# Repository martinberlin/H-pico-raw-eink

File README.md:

# H-pico-raw-eink

This is just a prototype PCB to test parallel eink signals with Raspberry PICO.

## Important To-Dos:

Find out if the pins selected for P-Mic signals and EINK signals behave correctly and are capable to do the job.

## Relevant datasheets

High voltages required by EPD P-Mic

https://www.ti.com/product/TPS65185

Eink signals described by Petteri Aimonen

http://essentialscrap.com/eink/waveforms.html

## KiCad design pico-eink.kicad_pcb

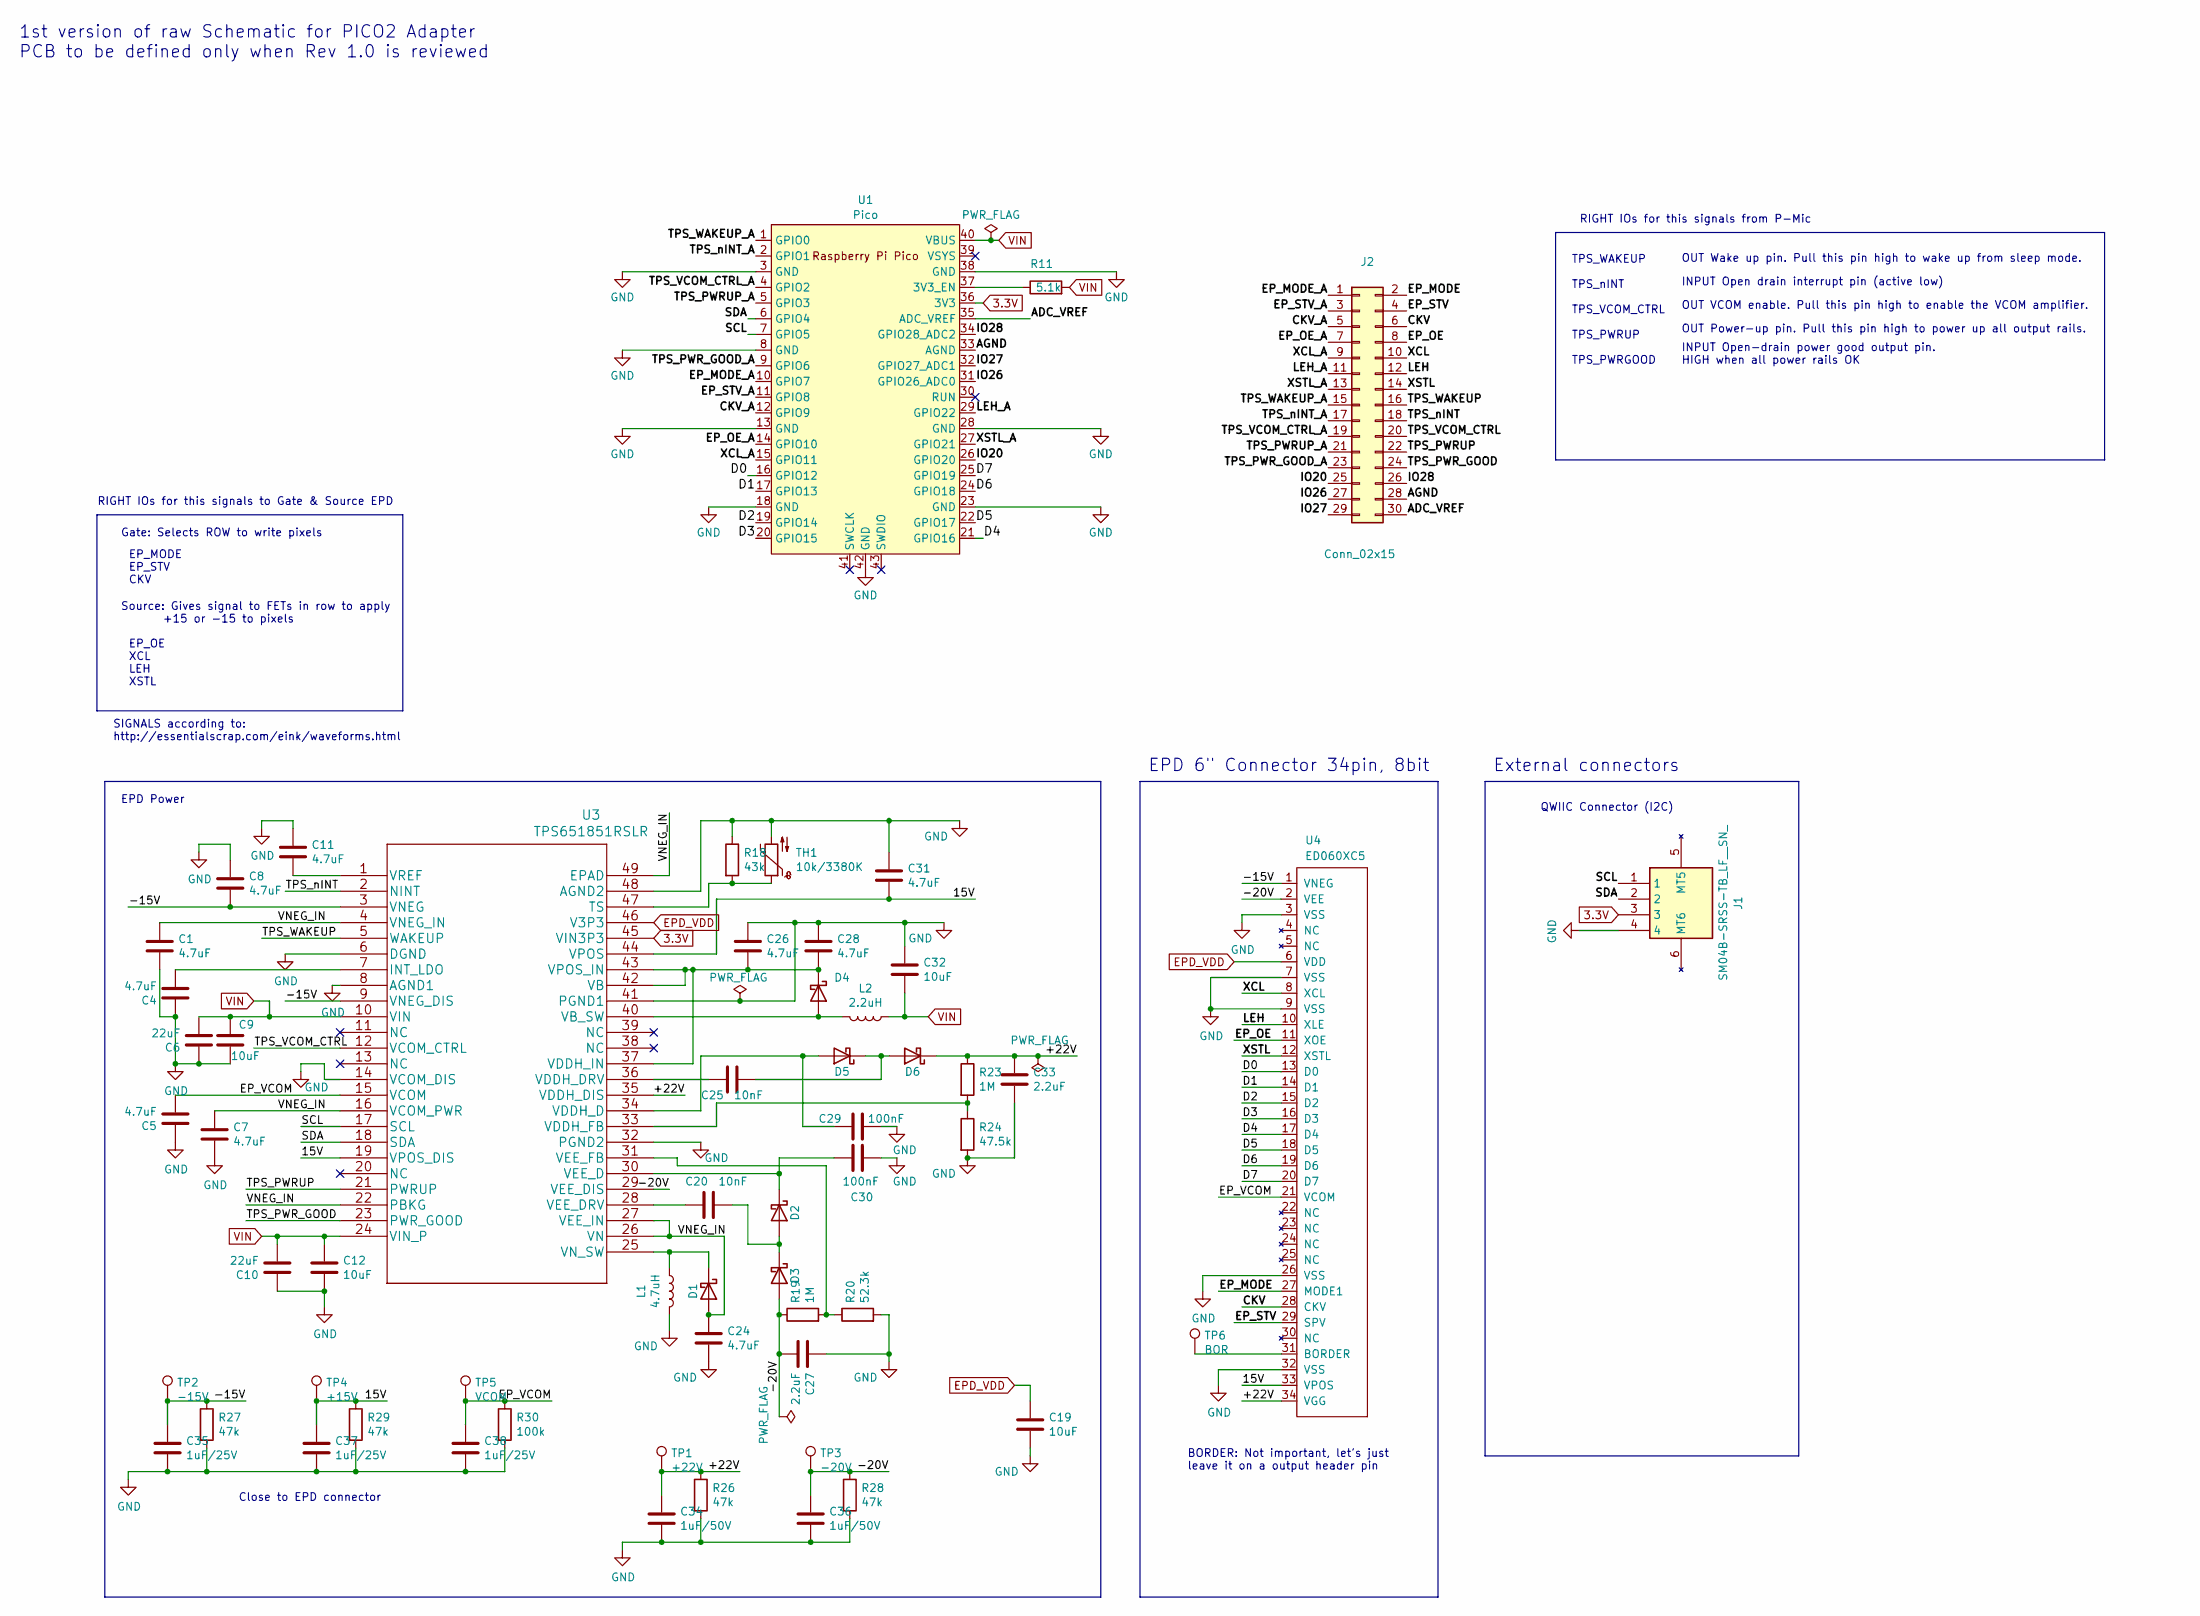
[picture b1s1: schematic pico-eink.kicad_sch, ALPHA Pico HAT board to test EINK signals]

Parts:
C1, C4, C5, C7, C8, C11, C24, C26, C28, C31: 4.7uF; C_0805_2012Metric; LCSC C1779
C6, C10: 22uF; C_0805_2012Metric; LCSC C45783
C9, C12, C19, C32: 10uF; C_0805_2012Metric; LCSC C15850
C20, C25: 10nF; C_0805_2012Metric; LCSC C1710
C27, C33: 2.2uF; C_0805_2012Metric; LCSC C49217
C29, C30: 100nF; C_0805_2012Metric; LCSC C49678
C34, C36: 1uF/50V; C_1206_3216Metric; LCSC C1848
C35, C37, C38: 1uF/25V; C_0805_2012Metric; LCSC C28323
D1, D2, D3, D4, D5, D6: MBR0540; D_SOD-123; LCSC C21353
J1: SM04B-SRSS-TB_LF__SN_; QWIIC_SM04B-SRSS-TB_LFSN_; Manufacturer_Part_Number SM04B-SRSS-TB(LF)(SN); LCSC C160404
J2: Conn_02x15; PinHeader_2x15_P2.54mm_Vertical
L1: 4.7uH; L_Taiyo-Yuden_NR-50xx_HandSoldering; LCSC C222947
L2: 2.2uH; L_Taiyo-Yuden_NR-40xx_HandSoldering; LCSC C92959
R11: 5.1k; R_0603_1608Metric; LCSC C23186
R18: 43k; R_0603_1608Metric; LCSC C23172
R19, R23: 1M; R_0603_1608Metric; LCSC C22935
R20: 52.3k; R_0603_1608Metric; LCSC C23196
R24: 47.5k; R_0603_1608Metric; LCSC C25819
R26, R27, R28, R29: 47k; R_0603_1608Metric; LCSC C25819
R30: 100k; R_0603_1608Metric; LCSC C25803
TH1: 10k/3380K; R_0603_1608Metric; LCSC C76589
TP1: +22V; TestPoint_Pad_D2.5mm
TP2: -15V; TestPoint_Pad_D2.5mm
TP3: -20V; TestPoint_Pad_D2.5mm
TP4: +15V; TestPoint_Pad_D2.5mm
TP5: VCOM; TestPoint_Pad_D2.5mm
TP6: BOR; TestPoint_Pad_D2.5mm
U1: Pico; RPi_Pico_SMD_TH
U3: TPS651851RSLR; LCSC C139292
U4: ED060XC5; X05A20H34G; LCSC C528053

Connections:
3.3V: J1.3, U1.36 (3V3), U3.45 (VIN3P3)
/15V: C31.2, C37.1, R29.1, TP4.1, U3.19 (VPOS_DIS), U3.44 (VPOS), U4.33 (VPOS)
/+22V: C33.1, C34.1, D6.1 (K), R23.1, R26.1, TP1.1, U3.35 (VDDH_DIS), U4.34 (VGG)
/-15V: C8.2, C35.1, R27.1, TP2.1, U3.3 (VNEG), U3.9 (VNEG_DIS), U4.1 (VNEG)
/-20V: C27.2, C36.1, D3.2 (A), R19.1, R28.1, TP3.1, U3.29 (VEE_DIS), U4.2 (VEE)
/ADC_VREF: J2.30, U1.35 (ADC_VREF)
/AGND: J2.28, U1.33 (AGND)
/CKV: J2.6, U4.28 (CKV)
/CKV_A: J2.5, U1.12 (GPIO9)
/D0: U1.16 (GPIO12), U4.13 (D0)
/D1: U1.17 (GPIO13), U4.14 (D1)
/D2: U1.19 (GPIO14), U4.15 (D2)
/D3: U1.20 (GPIO15), U4.16 (D3)
/D4: U1.21 (GPIO16), U4.17 (D4)
/D5: U1.22 (GPIO17), U4.18 (D5)
/D6: U1.24 (GPIO18), U4.19 (D6)
/D7: U1.25 (GPIO19), U4.20 (D7)
/EP_MODE: J2.2, U4.27 (MODE1)
/EP_MODE_A: J2.1, U1.10 (GPIO7)
/EP_OE: J2.8, U4.11 (XOE)
/EP_OE_A: J2.7, U1.14 (GPIO10)
/EP_STV: J2.4, U4.29 (SPV)
/EP_STV_A: J2.3, U1.11 (GPIO8)
/EP_VCOM: C5.2, C38.1, R30.1, TP5.1, U3.15 (VCOM), U4.21 (VCOM)
/IO20: J2.25, U1.26 (GPIO20)
/IO26: J2.27, U1.31 (GPIO26_ADC0)
/IO27: J2.29, U1.32 (GPIO27_ADC1)
/IO28: J2.26, U1.34 (GPIO28_ADC2)
/LEH: J2.12, U4.10 (XLE)
/LEH_A: J2.11, U1.29 (GPIO22)
/SCL: J1.1, U1.7 (GPIO5), U3.17 (SCL)
/SDA: J1.2, U1.6 (GPIO4), U3.18 (SDA)
/TPS_PWRUP: J2.22, U3.21 (PWRUP)
/TPS_PWRUP_A: J2.21, U1.5 (GPIO3)
/TPS_PWR_GOOD: J2.24, U3.23 (PWR_GOOD)
/TPS_PWR_GOOD_A: J2.23, U1.9 (GPIO6)
/TPS_VCOM_CTRL: J2.20, U3.12 (VCOM_CTRL)
/TPS_VCOM_CTRL_A: J2.19, U1.4 (GPIO2)
/TPS_WAKEUP: J2.16, U3.5 (WAKEUP)
/TPS_WAKEUP_A: J2.15, U1.1 (GPIO0)
/TPS_nINT: J2.18, U3.2 (NINT)
/TPS_nINT_A: J2.17, U1.2 (GPIO1)
/VNEG_IN: C1.1, C7.1, C24.1, D1.2 (A), U3.4 (VNEG_IN), U3.16 (VCOM_PWR), U3.22 (PBKG), U3.26 (VN), U3.27 (VEE_IN), U3.49 (EPAD)
/XCL: J2.10, U4.8 (XCL)
/XCL_A: J2.9, U1.15 (GPIO11)
/XSTL: J2.14, U4.12 (XSTL)
/XSTL_A: J2.13, U1.27 (GPIO21)
EPD_VDD: C19.1, U3.46 (V3P3), U4.6 (VDD)
GND: C1.2, C4.1, C5.1, C6.1, C7.2, C8.1, C9.2, C10.1, C11.1, C12.2, C19.2, C24.2, C26.1, C27.1, C28.1, C29.1, C30.2, C31.1, C32.1, C33.2, C34.2, C35.2, C36.2, C37.2, C38.2, J1.4, L1.2, R18.1, R20.2, R24.2, R26.2, R27.2, R28.2, R29.2, R30.2, TH1.2, U1.3 (GND), U1.8 (GND), U1.13 (GND), U1.18 (GND), U1.23 (GND), U1.28 (GND), U1.38 (GND), U1.42 (GND), U3.6 (DGND), U3.8 (AGND1), U3.14 (VCOM_DIS), U3.32 (PGND2), U3.41 (PGND1), U3.48 (AGND2), U4.3 (VSS), U4.7 (VSS), U4.9 (VSS), U4.26 (VSS), U4.32 (VSS)
unnamed: D1.1 (K), L1.1, U3.25 (VN_SW)
unnamed: C20.1, D2.2 (A), D3.1 (K)
unnamed: C30.1, D2.1 (K), U3.30 (VEE_D)
unnamed: D4.2 (A), L2.2, U3.40 (VB_SW)
unnamed: C26.2, C28.2, D4.1 (K), U3.37 (VDDH_IN), U3.42 (VB), U3.43 (VPOS_IN)
unnamed: C29.2, D5.2 (A), U3.34 (VDDH_D)
unnamed: C25.1, D5.1 (K), D6.2 (A)
unnamed: R11.1, U1.37 (3V3_EN)
unnamed: C4.2, U3.7 (INT_LDO)
unnamed: R18.2, TH1.1, U3.47 (TS)
unnamed: C25.2, U3.36 (VDDH_DRV)
unnamed: R23.2, R24.1, U3.33 (VDDH_FB)
unnamed: C20.2, U3.28 (VEE_DRV)
unnamed: R19.2, R20.1, U3.31 (VEE_FB)
unnamed: C11.2, U3.1 (VREF)
unnamed: TP6.1, U4.31 (BORDER)
VIN: C6.2, C9.1, C10.2, C12.1, C32.2, L2.1, R11.2, U1.40 (VBUS), U3.10 (VIN), U3.24 (VIN_P)

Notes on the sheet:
BORDER: Not important, let's just leave it on a output header pin
Gate: Selects ROW to write pixels
Close to EPD connector
TPS_WAKEUP TPS_nINT TPS_VCOM_CTRL TPS_PWRUP TPS_PWRGOOD
EPD 6" Connector 34pin, 8bit
INPUT Open drain interrupt pin (active low)
SIGNALS according to: http://essentialscrap.com/eink/waveforms.html
Source: Gives signal to FETs in row to apply +15 or -15 to pixels
RIGHT IOs for this signals to Gate & Source EPD
INPUT Open-drain power good output pin. HIGH when all power rails OK
OUT VCOM enable. Pull this pin high to enable the VCOM amplifier.
QWIIC Connector (I2C)
EPD Power
RIGHT IOs for this signals from P-Mic
OUT Wake up pin. Pull this pin high to wake up from sleep mode.
1st version of raw Schematic for PICO2 Adapter PCB to be defined only when Rev 1.0 is reviewed
EP_OE XCL LEH XSTL
EP_MODE EP_STV CKV
External connectors
OUT Power-up pin. Pull this pin high to power up all output rails.

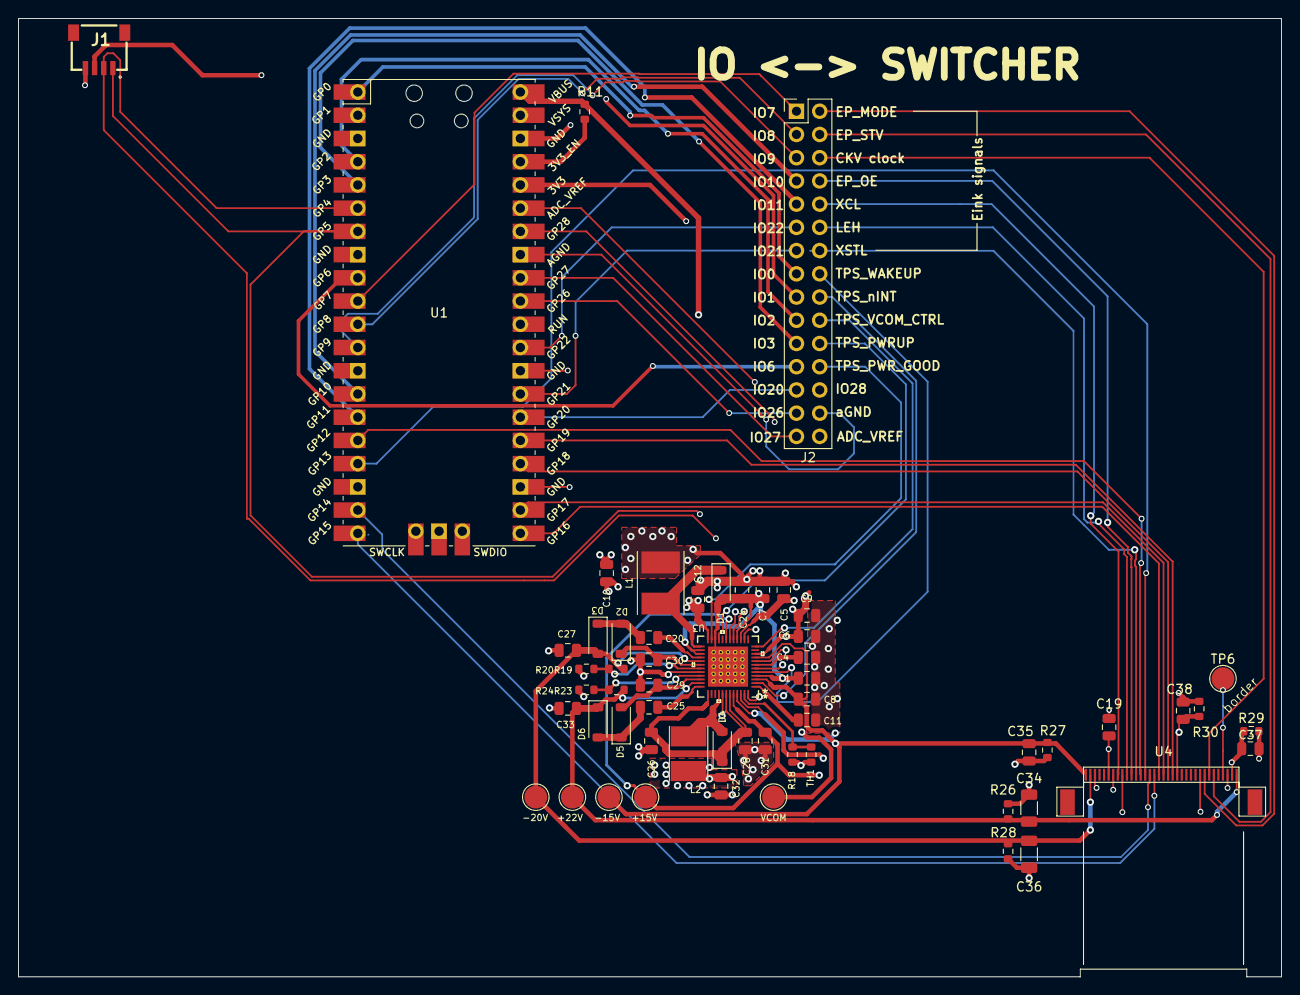
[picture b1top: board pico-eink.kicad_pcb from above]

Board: 4 copper layers, 138.1 x 104.8 mm, 58 parts (0 on the bottom side), 66 nets.

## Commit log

2024-08-19 Add 1st raw schematic
2024-08-19 Add QWIIC
2024-08-20 1st raw version, no DRM passed

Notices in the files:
parts and their libraries:
Copyright 2016 Accelerated Designs. All rights reserved.
